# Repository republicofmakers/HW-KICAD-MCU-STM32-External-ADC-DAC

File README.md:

# Mixed Signal Hardware Design

Image generated with Kicad 3D viewer.
  <br />
  
* You can download and check the project in Kicad.
* You can order this board (incl. SMT assembly) at https://www.jlcpcb.com. 
* Gerber and assembly files are in the relevant repo folders.

# With this project you can learn how to design:
* Switching voltage regulator and Low-dropout regulator
* STM32 MCU that using USB & SPI interface
* ADC / DAC integration
* Creating kalman filter for noise
* Also how to isolate the part with PCB cutouts for noise

NOTE:If you are an employer , you can check out my skills...

# Where can you use it?
* If you need many ADC or DAC readings, STM32 have limited number of ADC/DAC , such as if you design an SDD tester etc. 
* If you need more accurate readings, I used 14-Bit for ADC and 12-Bit for DAC but you can go 16-BIT or more...
* ADC => (ADC141S626 14-Bit, 50 kSPS to 250 kSPS)
* DAC => (DAC7563SDGSR 12-Bit, 0 to 3.3V)
* I used these parts because I had at my invertory, but I think you get the idea.
* If you need filtering for noise, kalman filters are so common in industry. Drones etc.<br />
Don't forget the test with LTSPICE.
<br />
<br />
* Take the project, adapt it , use it. I hope it helps you...

<br />
<br />

 **STM32F1 based ADC / DAC signal analyzer** 

 **Mixed Signal Hardware Design with Kicad** 

 **Created By Ceyhun Pempeci**

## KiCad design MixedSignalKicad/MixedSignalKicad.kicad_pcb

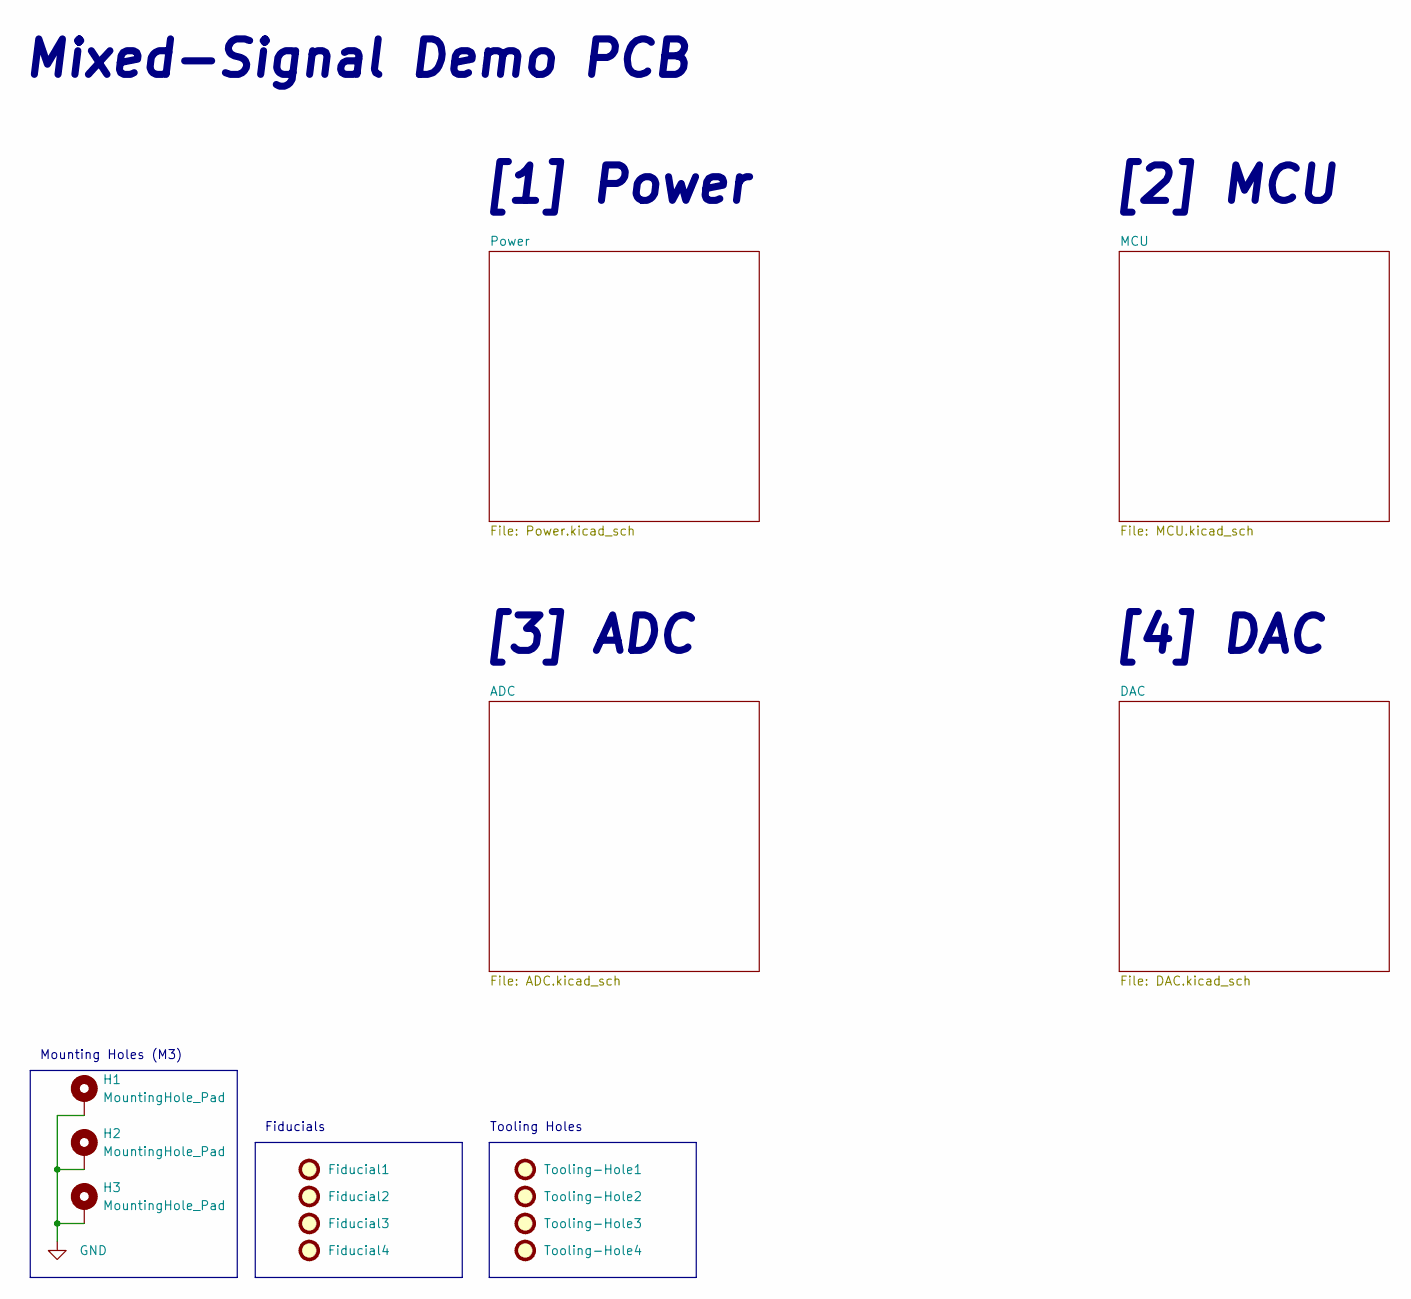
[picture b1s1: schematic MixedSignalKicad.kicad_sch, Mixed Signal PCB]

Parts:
Fiducial1, Fiducial2, Fiducial3, Fiducial4: Fiducial_1mm_Mask2mm
H1, H2, H3: MountingHole_Pad; MountingHole_3.2mm_M3_Pad_Via
Tooling-Hole1, Tooling-Hole2, Tooling-Hole3, Tooling-Hole4: ToolingHole

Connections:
GND: H1.1, H2.1, H3.1; also elsewhere on the board

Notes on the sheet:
[4] DAC
Mixed-Signal Demo PCB
Fiducials
[3] ADC
Mounting Holes (M3)
[2] MCU
Tooling Holes
[1] Power

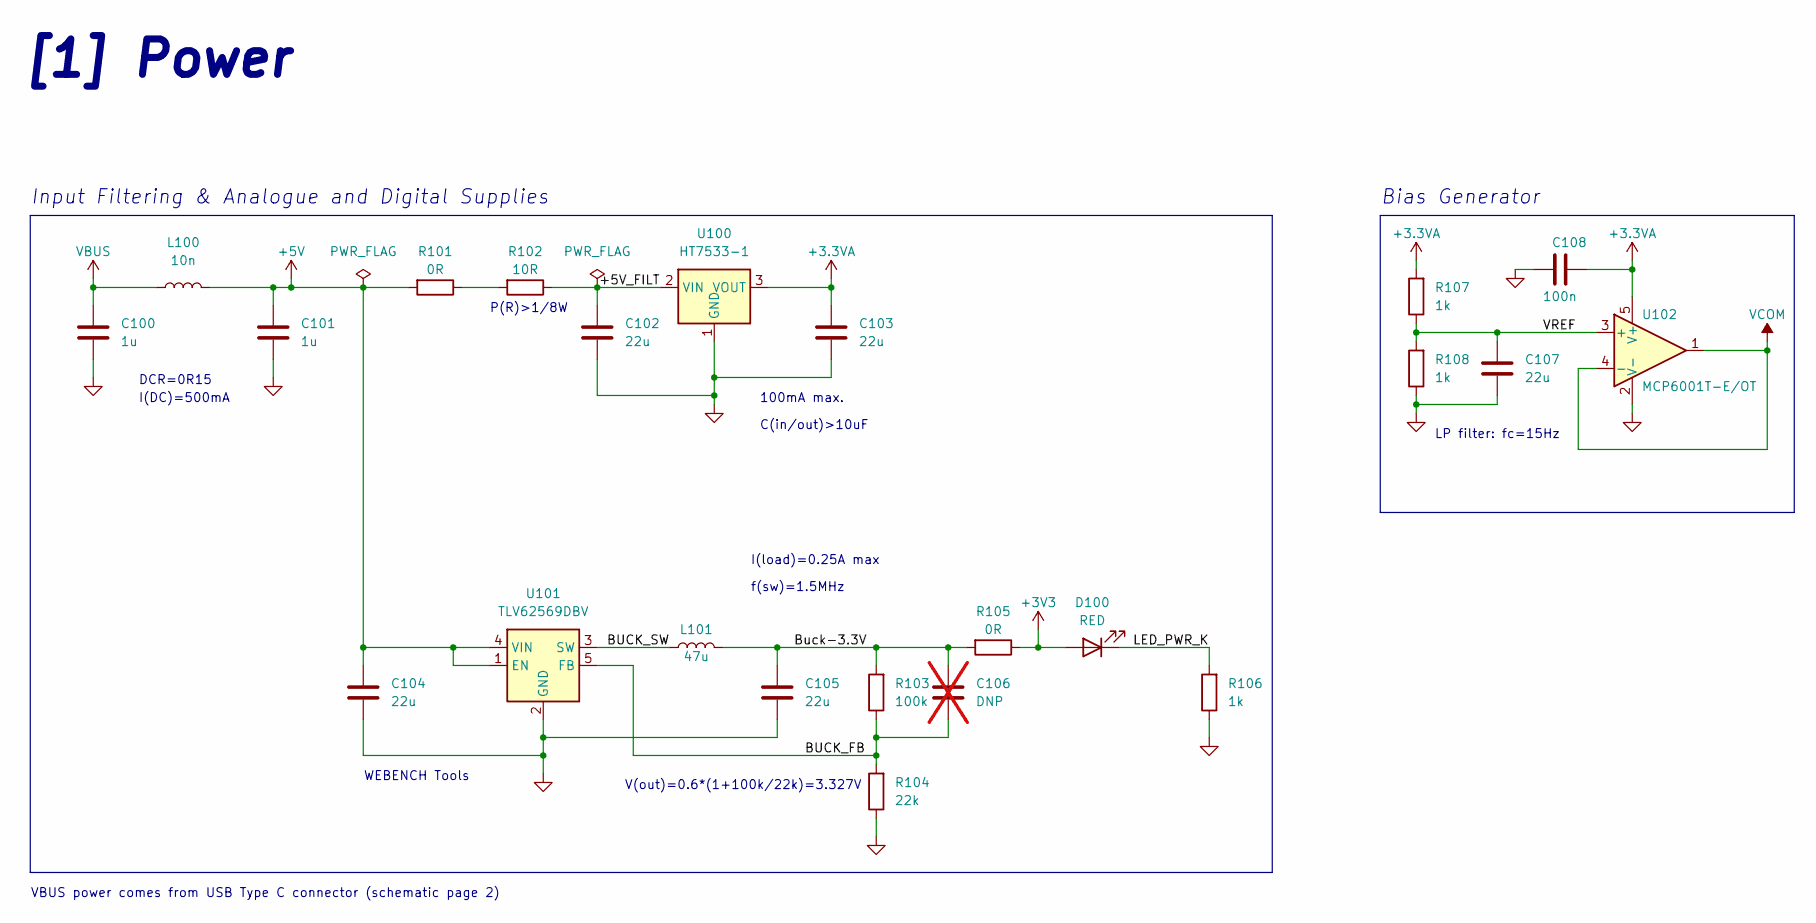
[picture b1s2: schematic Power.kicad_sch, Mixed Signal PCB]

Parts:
C100, C101: 1u; C_0603_1608Metric; LCSC C15849
C102, C103, C104, C105, C107: 22u; C_0805_2012Metric; LCSC C377773
C106: DNP; C_0402_1005Metric; not fitted
C108: 100n; C_0402_1005Metric; LCSC C1525
D100: RED; LED_0603_1608Metric; LCSC C2286
L100: 10n; L_0402_1005Metric; LCSC C27147
L101: 47u; MWSA0603S; LCSC C408455
R101, R105: 0R; R_2010_5025Metric; LCSC C270958
R102: 10R; R_2010_5025Metric; LCSC C324069
R103: 100k; R_0402_1005Metric; LCSC C25741
R104: 22k; R_0402_1005Metric; LCSC C25768
R106, R107, R108: 1k; R_0402_1005Metric; LCSC C11702
U100: HT7533-1; SOT-89-3; LCSC C14289
U101: TLV62569DBV; SOT-23-5; LCSC C141836
U102: MCP6001T-E/OT; SOT-23-5; LCSC C29429

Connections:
+3.3VA: C103.1, C108.1, R107.2, U100.3 (VOUT), U102.5 (V+); also elsewhere on the board
+3V3: D100.2 (A), R105.1; also elsewhere on the board
+5V: C101.1, C104.1, L100.2, R101.2, U101.1 (EN), U101.4 (VIN); also elsewhere on the board
/Power/+5V_FILT: C102.1, R102.1, U100.2 (VIN)
/Power/BUCK_FB: C106.2, R103.1, R104.2, U101.5 (FB)
/Power/BUCK_SW: L101.1, U101.3 (SW)
/Power/Buck-3.3V: C105.1, C106.1, L101.2, R103.2, R105.2
/Power/LED_PWR_K: D100.1 (K), R106.2
/Power/VREF: C107.1, R107.1, R108.2, U102.3 (+)
GND: C100.2, C101.2, C102.2, C103.2, C104.2, C105.2, C107.2, C108.2, R104.1, R106.1, R108.1, U100.1 (GND), U101.2 (GND), U102.2 (V-); also elsewhere on the board
unnamed: R101.1, R102.2
VBUS: C100.1, L100.1; also elsewhere on the board
VCOM: U102.1, U102.4 (-); also elsewhere on the board

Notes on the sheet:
DCR=0R15
C(in/out)>10uF
V(out)=0.6*(1+100k/22k)=3.327V
I(DC)=500mA
Bias Generator
LP filter: fc=15Hz
100mA max.
f(sw)=1.5MHz
VBUS power comes from USB Type C connector (schematic page 2)
P(R)>1/8W
I(load)=0.25A max
Input Filtering & Analogue and Digital Supplies
[1] Power
WEBENCH Tools

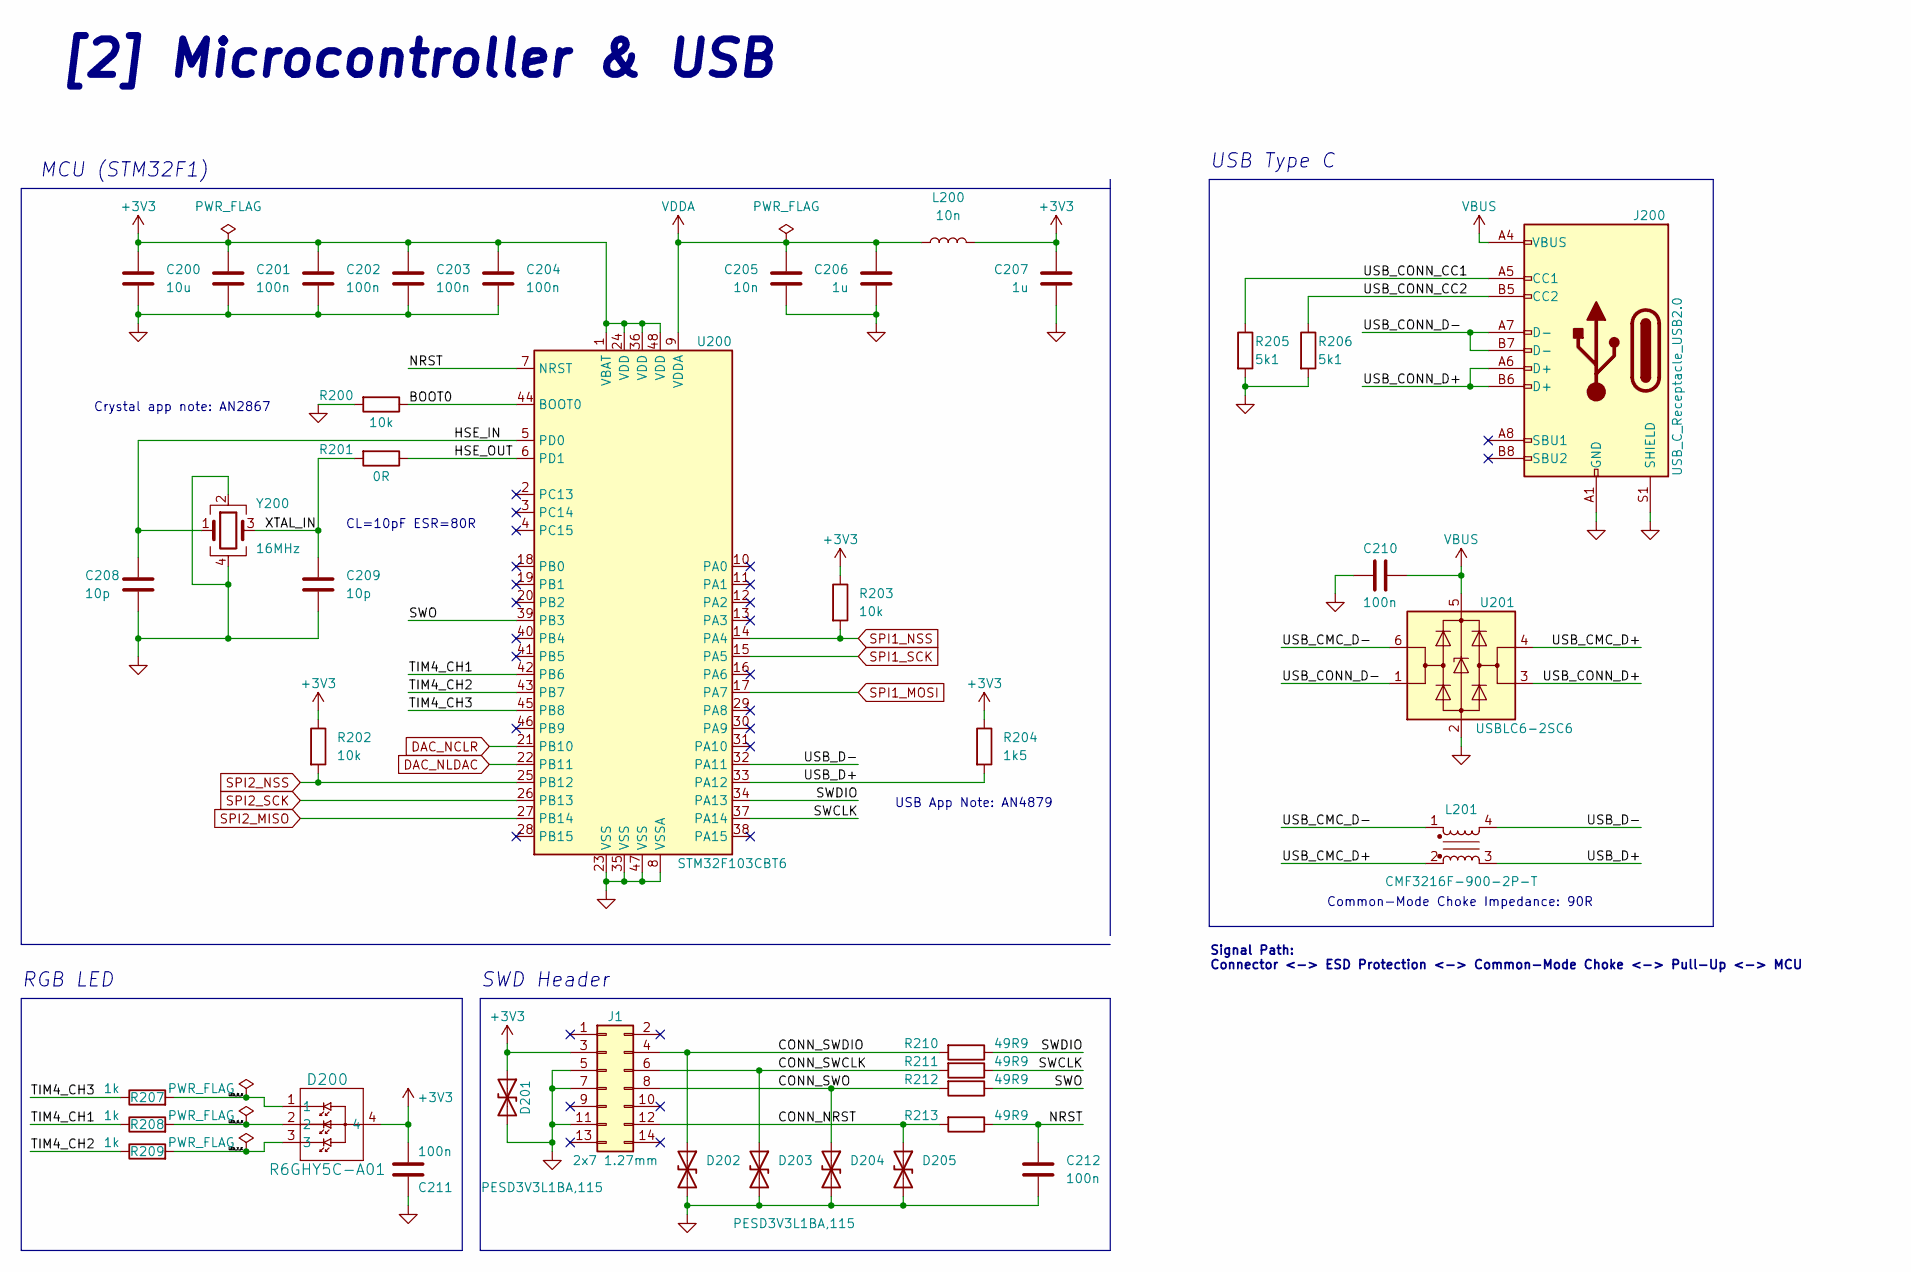
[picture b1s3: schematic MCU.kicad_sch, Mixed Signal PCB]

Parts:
C200: 10u; C_0603_1608Metric; LCSC C19702
C201, C202, C203, C204, C210, C211, C212: 100n; C_0402_1005Metric; LCSC C1525
C205: 10n; C_0402_1005Metric; LCSC C15195
C206, C207: 1u; C_0603_1608Metric; LCSC C15849
C208, C209: 10p; C_0402_1005Metric; LCSC C32949
D200: R6GHY5C-A01; LCSC C2897364
D201, D202, D203, D204, D205: PESD3V3L1BA,115; D_SOD-323; LCSC C51450
J1: 2x7 1.27mm; 14 Pin IDC 1.27mm; LCSC C2935955
J200: USB_C_Receptacle_USB2.0; TYPE-C-31-M-12; LCSC C165948
L200: 10n; L_0402_1005Metric; LCSC C27147
L201: CMF3216F-900-2P-T; CMC-1206; LCSC C963740
R200, R202, R203: 10k; R_0402_1005Metric; LCSC C25744
R201: 0R; R_0402_1005Metric; LCSC C17168
R204: 1k5; R_0402_1005Metric; LCSC C25867
R205, R206: 5k1; R_0402_1005Metric; LCSC C25905
R207, R208, R209: 1k; R_0402_1005Metric; LCSC C11702
R210, R211, R212, R213: 49R9; R_0402_1005Metric; LCSC C25120
U200: STM32F103CBT6; LQFP-48_7x7mm_P0.5mm; LCSC C8304
U201: USBLC6-2SC6; SOT-23-6; LCSC C7519
Y200: 16MHz; Crystal_SMD_3225-4Pin_3.2x2.5mm; LCSC C13738

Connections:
+3V3: C200.1, C201.1, C202.1, C203.1, C204.1, C207.1, C211.1, D200.4, D201.1 (A1), L200.2, R202.1, R203.1, R204.1, U200.1 (VBAT), U200.24 (VDD), U200.36 (VDD), U200.48 (VDD); also elsewhere on the board
/MCU/BOOT0: R200.1, U200.44 (BOOT0)
/MCU/CONN_NRST: D205.1 (A1), R213.2; also elsewhere on the board
/MCU/CONN_SWCLK: D203.1 (A1), R211.2; also elsewhere on the board
/MCU/CONN_SWDIO: D202.1 (A1), R210.2; also elsewhere on the board
/MCU/CONN_SWO: D204.1 (A1), R212.2; also elsewhere on the board
/MCU/HSE_IN: C208.1, U200.5 (PD0), Y200.1
/MCU/HSE_OUT: R201.1, U200.6 (PD1)
/MCU/LED_G_K: D200.2, R208.2
/MCU/LED_R_K: D200.1, R207.2
/MCU/LED_Y_K: D200.3, R209.2
/MCU/NRST: C212.1, R213.1, U200.7 (NRST)
/MCU/SWCLK: R211.1, U200.37 (PA14)
/MCU/SWDIO: R210.1, U200.34 (PA13)
/MCU/SWO: R212.1, U200.39 (PB3)
/MCU/TIM4_CH1: R208.1, U200.42 (PB6)
/MCU/TIM4_CH2: R209.1, U200.43 (PB7)
/MCU/TIM4_CH3: R207.1, U200.45 (PB8)
/MCU/USB_CMC_D+: L201.2, U201.4 (I/O2)
/MCU/USB_CMC_D-: L201.1, U201.6 (I/O1)
/MCU/USB_CONN_CC1: J200.A5 (CC1), R205.1
/MCU/USB_CONN_CC2: J200.B5 (CC2), R206.1
/MCU/USB_CONN_D+: J200.A6 (D+), J200.B6 (D+), U201.3 (I/O2)
/MCU/USB_CONN_D-: J200.A7 (D-), J200.B7 (D-), U201.1 (I/O1)
/MCU/USB_D+: L201.3, R204.2, U200.33 (PA12)
/MCU/USB_D-: L201.4, U200.32 (PA11)
/MCU/XTAL_IN: C209.1, R201.2, Y200.3
DAC_NCLR: U200.21 (PB10); also elsewhere on the board
DAC_NLDAC: U200.22 (PB11); also elsewhere on the board
GND: C200.2, C201.2, C202.2, C203.2, C204.2, C205.2, C206.2, C207.2, C208.2, C209.2, C210.2, C211.2, C212.2, D201.2 (A2), D202.2 (A2), D203.2 (A2), D204.2 (A2), D205.2 (A2), J200.A1 (GND), J200.A12 (GND), J200.B1 (GND), J200.B12 (GND), J200.S1 (SHIELD), R200.2, R205.2, R206.2, U200.8 (VSSA), U200.23 (VSS), U200.35 (VSS), U200.47 (VSS), U201.2 (GND), Y200.2, Y200.4; also elsewhere on the board
SPI1_MOSI: U200.17 (PA7); also elsewhere on the board
SPI1_NSS: R203.2, U200.14 (PA4); also elsewhere on the board
SPI1_SCK: U200.15 (PA5); also elsewhere on the board
SPI2_MISO: U200.27 (PB14); also elsewhere on the board
SPI2_NSS: R202.2, U200.25 (PB12); also elsewhere on the board
SPI2_SCK: U200.26 (PB13); also elsewhere on the board
VBUS: C210.1, J200.A4 (VBUS), J200.A9 (VBUS), J200.B4 (VBUS), J200.B9 (VBUS), U201.5 (VBUS); also elsewhere on the board
VDDA: C205.1, C206.1, L200.1, U200.9 (VDDA)

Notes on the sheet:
Signal Path: Connector <-> ESD Protection <-> Common-Mode Choke <-> Pull-Up <-> MCU
RGB LED
Crystal app note: AN2867
SWD Header
USB App Note: AN4879
Common-Mode Choke Impedance: 90R
[2] Microcontroller & USB
CL=10pF ESR=80R
MCU (STM32F1)
USB Type C

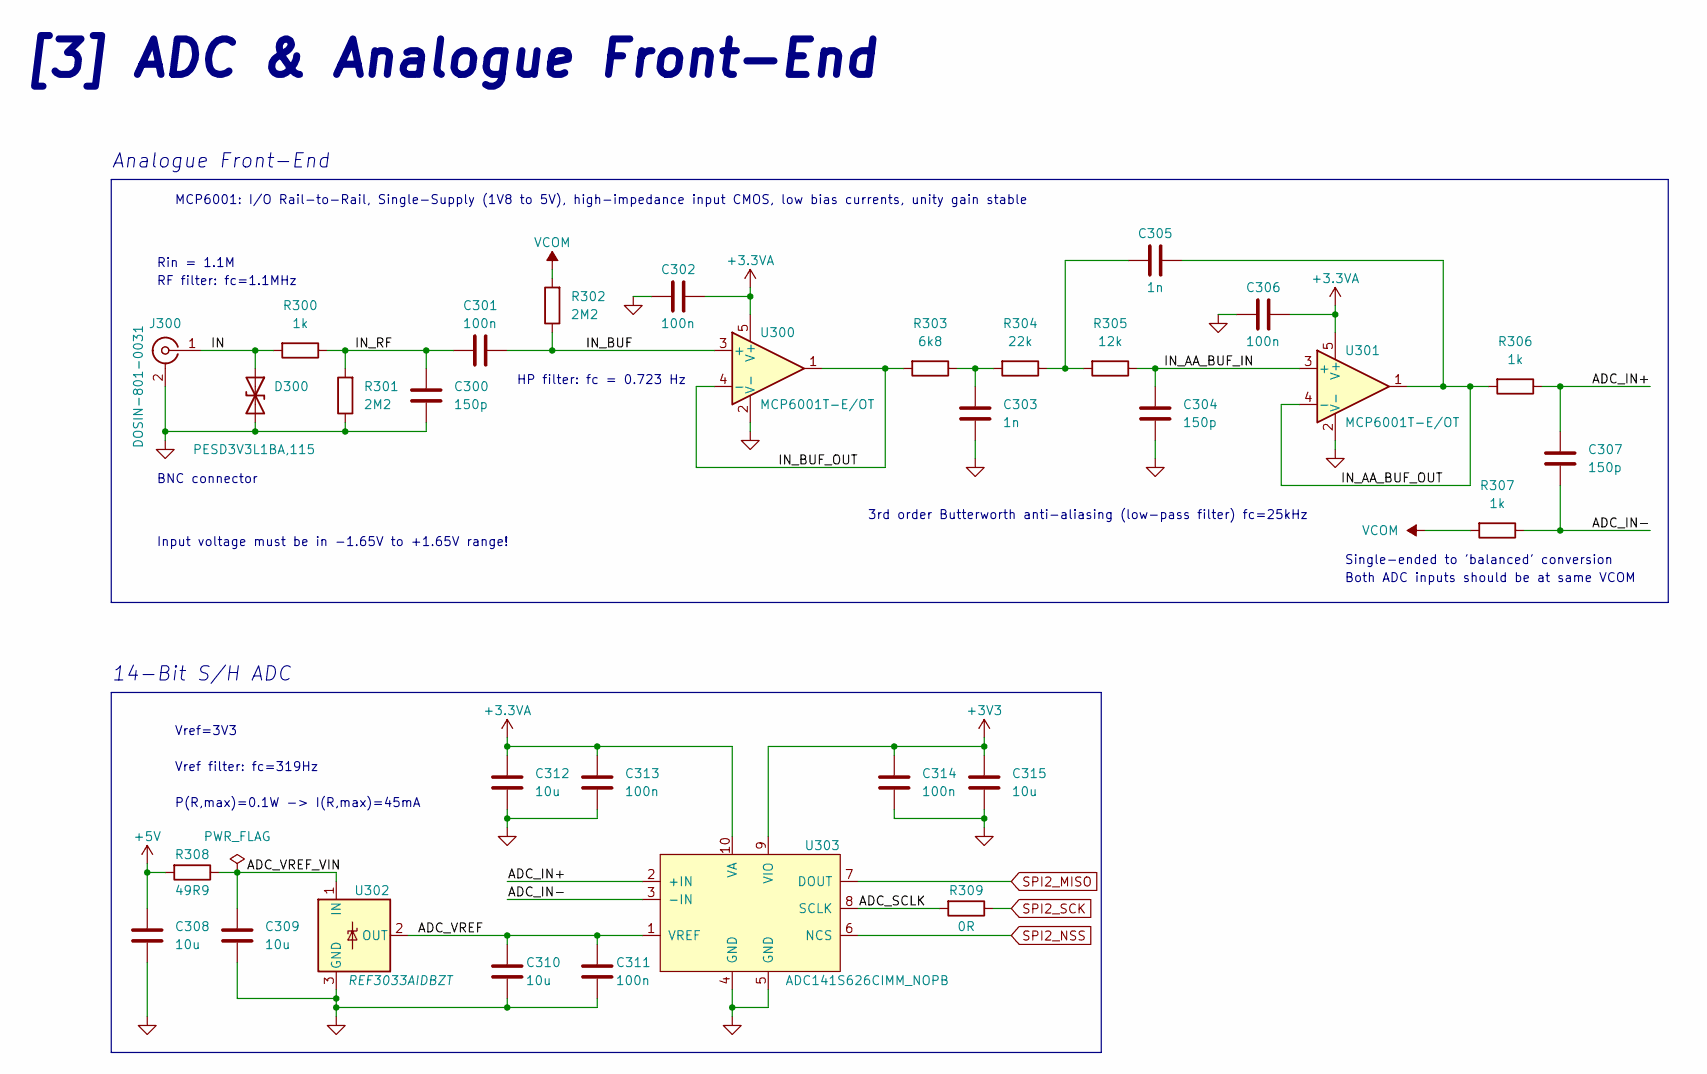
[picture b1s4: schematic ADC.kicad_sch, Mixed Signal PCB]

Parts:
C300, C304, C307: 150p; C_0402_1005Metric; LCSC C106998
C301, C302, C306, C311, C313, C314: 100n; C_0402_1005Metric; LCSC C1525
C303, C305: 1n; C_0402_1005Metric; LCSC C1523
C308, C309, C310, C312, C315: 10u; C_0603_1608Metric; LCSC C19702
D300: PESD3V3L1BA,115; D_SOD-323; LCSC C51450
J300: DOSIN-801-0031; AMPHENOL-BNC-031-5640-1010; LCSC C521205
R300, R306, R307: 1k; R_0402_1005Metric; LCSC C11702
R301, R302: 2M2; R_0402_1005Metric; LCSC C274901
R303: 6k8; R_0402_1005Metric; LCSC C25917
R304: 22k; R_0402_1005Metric; LCSC C25768
R305: 12k; R_0402_1005Metric; LCSC C25752
R308: 49R9; R_0402_1005Metric; LCSC C25120
R309: 0R; R_0402_1005Metric; LCSC C17168
U300, U301: MCP6001T-E/OT; SOT-23-5; LCSC C29429
U302: REF3033AIDBZT; SOT-23; LCSC C2872391
U303: ADC141S626CIMM_NOPB; VSSOP-10; LCSC C206494

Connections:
+3.3VA: C302.1, C306.1, C312.1, C313.1, U300.5 (V+), U301.5 (V+), U303.10 (VA); also elsewhere on the board
+3V3: C314.1, C315.1, U303.9 (VIO); also elsewhere on the board
+5V: C308.1, R308.2; also elsewhere on the board
/ADC/ADC_IN+: C307.1, R306.1, U303.2 (+IN)
/ADC/ADC_IN-: C307.2, R307.1, U303.3 (-IN)
/ADC/ADC_SCLK: R309.2, U303.8 (SCLK)
/ADC/ADC_VREF: C310.1, C311.1, U302.2 (OUT), U303.1 (VREF)
/ADC/ADC_VREF_VIN: C309.1, R308.1, U302.1 (IN)
/ADC/IN: D300.1 (A1), J300.1 (In), R300.2
/ADC/IN_AA_BUF_IN: C304.1, R305.1, U301.3 (+)
/ADC/IN_AA_BUF_OUT: C305.2, R306.2, U301.1, U301.4 (-)
/ADC/IN_BUF: C301.1, R302.1, U300.3 (+)
/ADC/IN_BUF_OUT: R303.2, U300.1, U300.4 (-)
/ADC/IN_RF: C300.1, C301.2, R300.1, R301.2
GND: C300.2, C302.2, C303.2, C304.2, C306.2, C308.2, C309.2, C310.2, C311.2, C312.2, C313.2, C314.2, C315.2, D300.2 (A2), J300.2 (Ext), R301.1, U300.2 (V-), U301.2 (V-), U302.3 (GND), U303.4 (GND), U303.5 (GND); also elsewhere on the board
unnamed: C303.1, R303.1, R304.2
unnamed: C305.1, R304.1, R305.2
SPI2_MISO: U303.7 (DOUT); also elsewhere on the board
SPI2_NSS: U303.6 (NCS); also elsewhere on the board
SPI2_SCK: R309.1; also elsewhere on the board
VCOM: R302.2, R307.2; also elsewhere on the board

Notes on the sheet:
HP filter: fc = 0.723 Hz
Both ADC inputs should be at same VCOM
BNC connector
Rin = 1.1M
14-Bit S/H ADC
Vref filter: fc=319Hz
Input voltage must be in -1.65V to +1.65V range!
Analogue Front-End
Single-ended to 'balanced' conversion
RF filter: fc=1.1MHz
3rd order Butterworth anti-aliasing (low-pass filter) fc=25kHz
MCP6001: I/O Rail-to-Rail, Single-Supply (1V8 to 5V), high-impedance input CMOS, low bias currents, unity gain stable
P(R,max)=0.1W -> I(R,max)=45mA
Vref=3V3
[3] ADC & Analogue Front-End

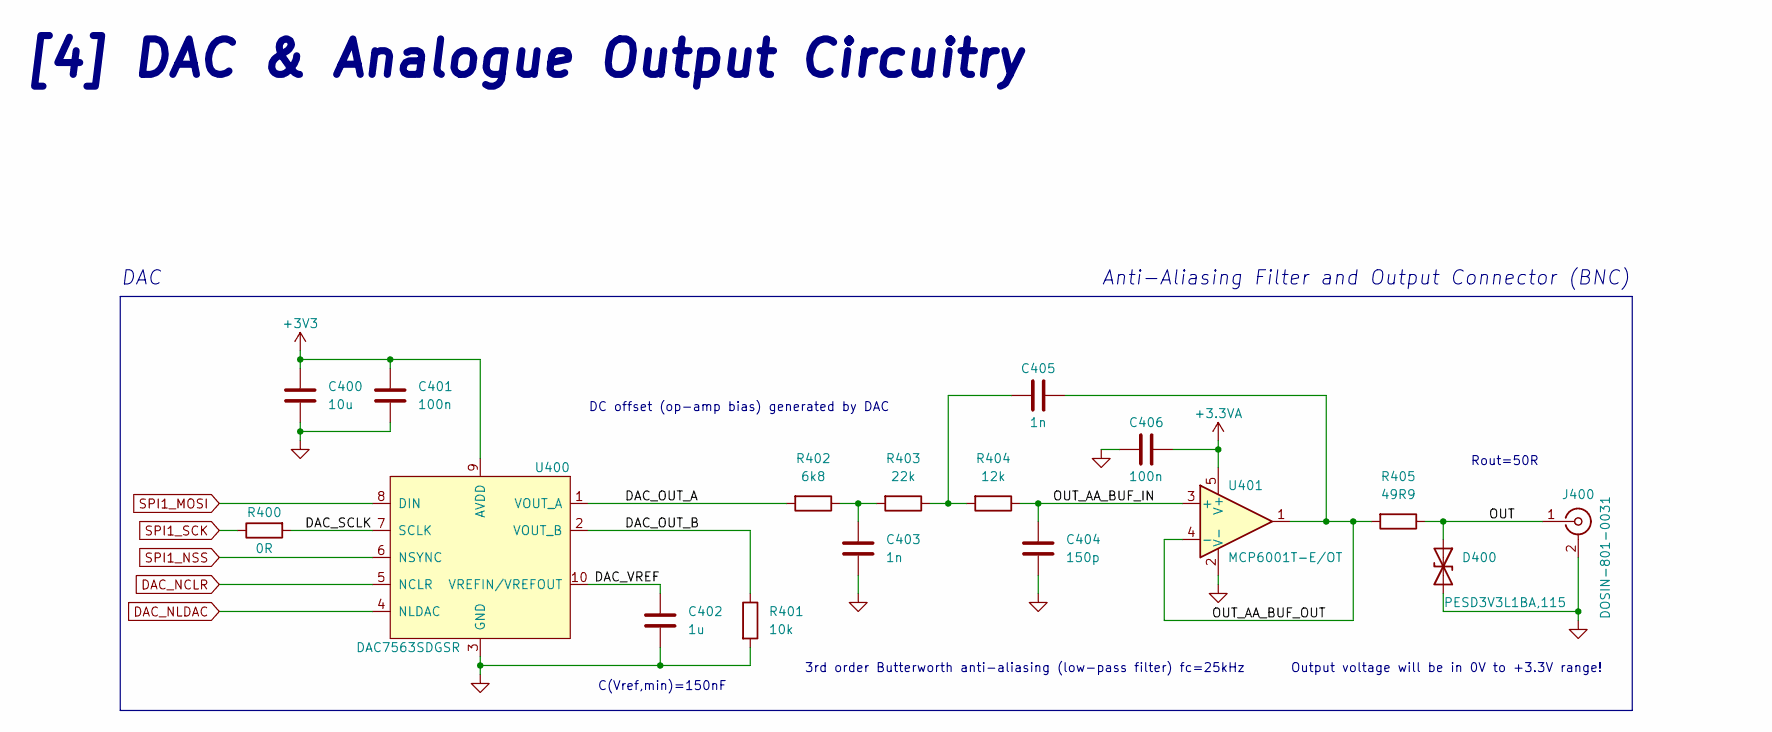
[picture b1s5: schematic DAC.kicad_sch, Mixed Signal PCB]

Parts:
C400: 10u; C_0603_1608Metric; LCSC C19702
C401, C406: 100n; C_0402_1005Metric; LCSC C1525
C402: 1u; C_0603_1608Metric; LCSC C15849
C403, C405: 1n; C_0402_1005Metric; LCSC C1523
C404: 150p; C_0402_1005Metric; LCSC C106998
D400: PESD3V3L1BA,115; D_SOD-323; LCSC C51450
J400: DOSIN-801-0031; AMPHENOL-BNC-031-5640-1010; LCSC C521205
R400: 0R; R_0402_1005Metric; LCSC C17168
R401: 10k; R_0402_1005Metric; LCSC C25744
R402: 6k8; R_0402_1005Metric; LCSC C25917
R403: 22k; R_0402_1005Metric; LCSC C25768
R404: 12k; R_0402_1005Metric; LCSC C25752
R405: 49R9; R_0402_1005Metric; LCSC C25120
U400: DAC7563SDGSR; VSSOP-10; LCSC C601656
U401: MCP6001T-E/OT; SOT-23-5; LCSC C29429

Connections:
+3.3VA: C406.1, U401.5 (V+); also elsewhere on the board
+3V3: C400.1, C401.1, U400.9 (AVDD); also elsewhere on the board
/DAC/DAC_OUT_A: R402.2, U400.1 (VOUT_A)
/DAC/DAC_OUT_B: R401.1, U400.2 (VOUT_B)
/DAC/DAC_SCLK: R400.2, U400.7 (SCLK)
/DAC/DAC_VREF: C402.1, U400.10 (VREFIN/VREFOUT)
/DAC/OUT: D400.1 (A1), J400.1 (In), R405.1
/DAC/OUT_AA_BUF_IN: C404.1, R404.1, U401.3 (+)
/DAC/OUT_AA_BUF_OUT: C405.2, R405.2, U401.1, U401.4 (-)
DAC_NCLR: U400.5 (NCLR); also elsewhere on the board
DAC_NLDAC: U400.4 (NLDAC); also elsewhere on the board
GND: C400.2, C401.2, C402.2, C403.2, C404.2, C406.2, D400.2 (A2), J400.2 (Ext), R401.2, U400.3 (GND), U401.2 (V-); also elsewhere on the board
unnamed: C403.1, R402.1, R403.2
unnamed: C405.1, R403.1, R404.2
SPI1_MOSI: U400.8 (DIN); also elsewhere on the board
SPI1_NSS: U400.6 (NSYNC); also elsewhere on the board
SPI1_SCK: R400.1; also elsewhere on the board

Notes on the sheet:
[4] DAC & Analogue Output Circuitry
Anti-Aliasing Filter and Output Connector (BNC)
Rout=50R
Output voltage will be in 0V to +3.3V range!
DAC
C(Vref,min)=150nF
3rd order Butterworth anti-aliasing (low-pass filter) fc=25kHz
DC offset (op-amp bias) generated by DAC

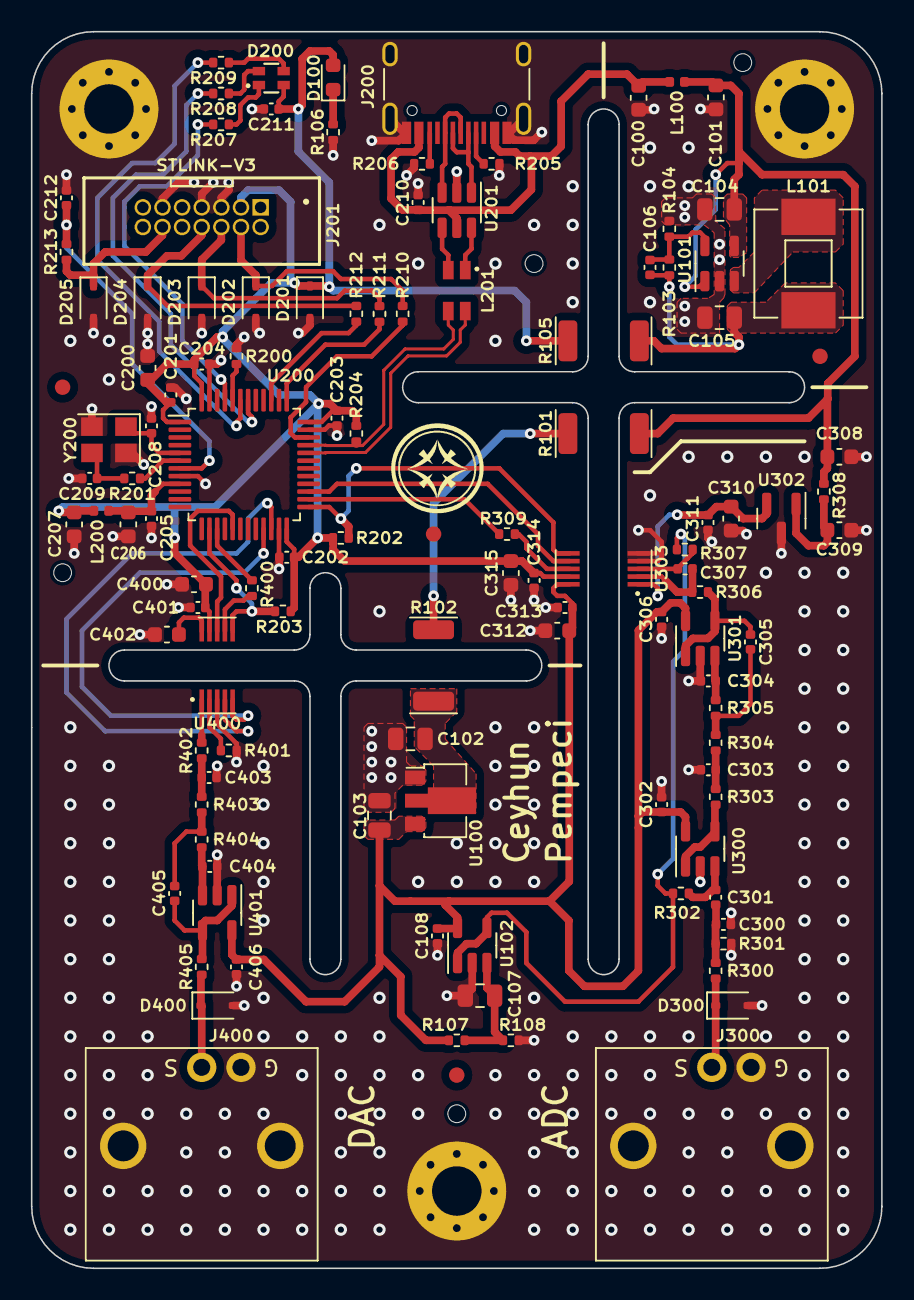
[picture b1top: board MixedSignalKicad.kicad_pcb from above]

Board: 2 copper layers, 55.0 x 80.0 mm, 123 parts (0 on the bottom side), 70 nets.

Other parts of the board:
J201: 2x7 1.27mm; 14 Pin IDC 1.27mm

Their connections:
+3V3: J201.3; also elsewhere on the board
/MCU/CONN_NRST: J201.12; also elsewhere on the board
/MCU/CONN_SWCLK: J201.6; also elsewhere on the board
/MCU/CONN_SWDIO: J201.4; also elsewhere on the board
/MCU/CONN_SWO: J201.8; also elsewhere on the board
GND: J201.5, J201.7, J201.11; also elsewhere on the board

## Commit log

2024-04-24 Update LICENSE
